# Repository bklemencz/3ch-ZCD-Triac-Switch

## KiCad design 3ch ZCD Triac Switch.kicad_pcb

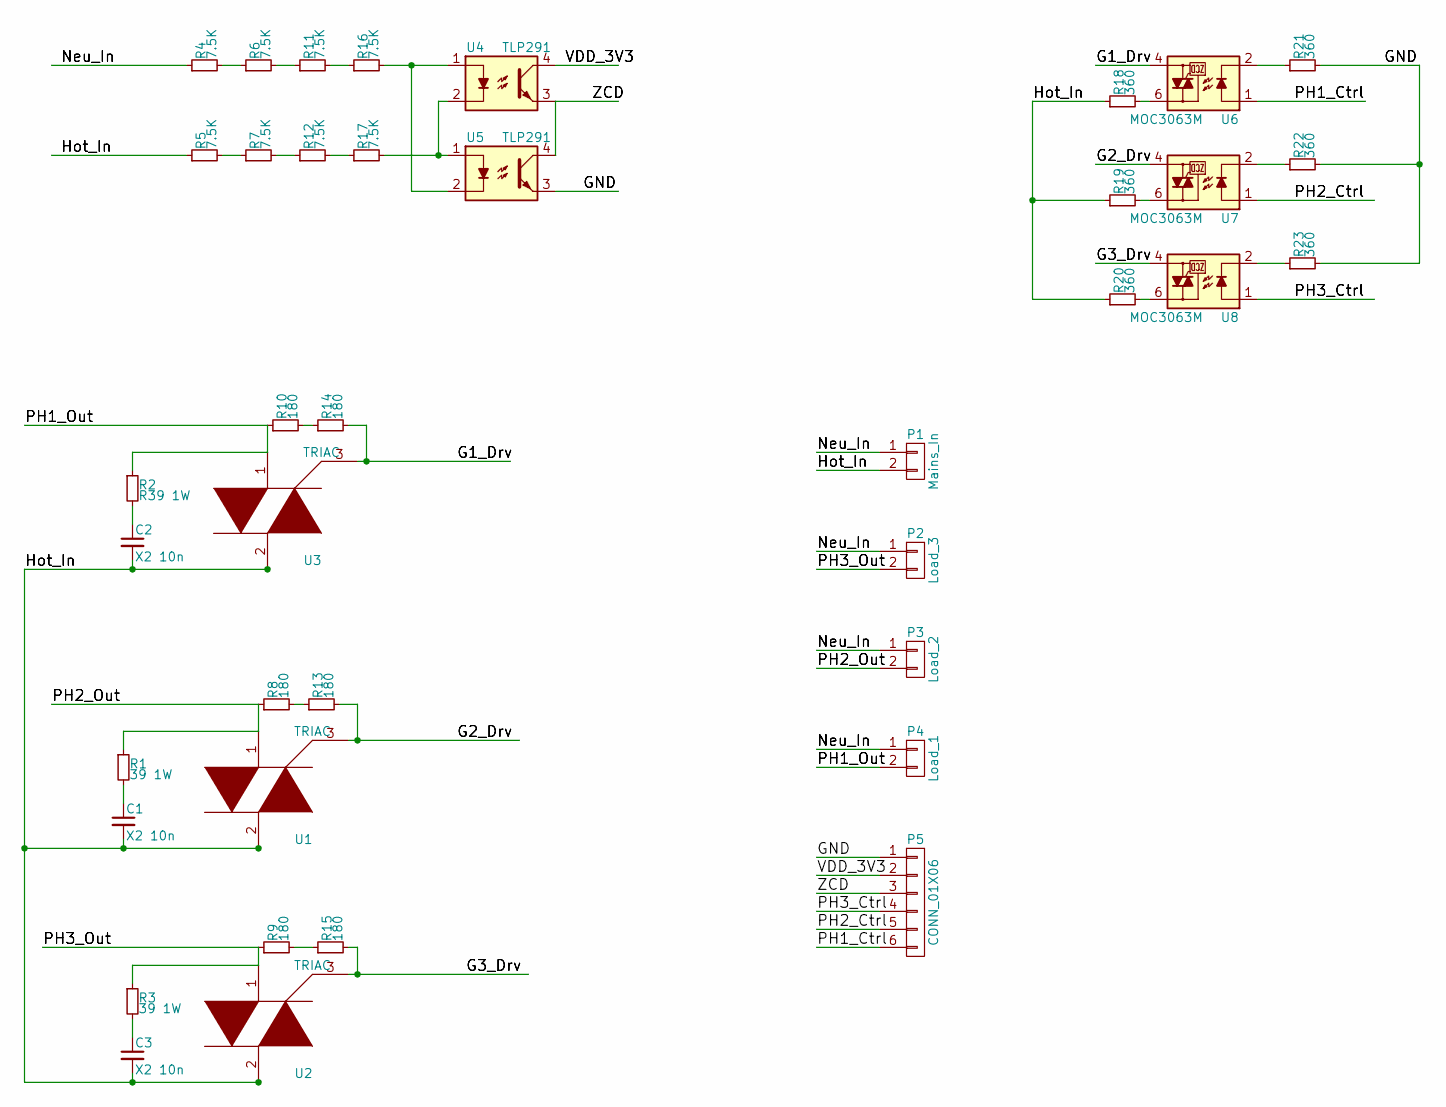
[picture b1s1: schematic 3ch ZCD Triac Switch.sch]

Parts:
C1, C2, C3: X2 10n; C_Rect_L13_W6_H12_P10
P1: Mains_In; TerminalBlock_Pheonix_MKDS1.5-2pol
P2: Load_3; TerminalBlock_Pheonix_MKDS1.5-2pol
P3: Load_2; TerminalBlock_Pheonix_MKDS1.5-2pol
P4: Load_1; TerminalBlock_Pheonix_MKDS1.5-2pol
P5: CONN_01X06; Pin_Header_Straight_1x06
R1, R3: 39 1W; Resistor_Horizontal_RM15mm
R2: R39 1W; Resistor_Horizontal_RM15mm
R4, R5, R6, R7, R11, R12, R16, R17: 7.5K; R_1206
R8, R9, R10, R13, R14, R15: 180; R_1206
R18, R19, R20, R21, R22, R23: 360; R_1206
U1, U2, U3: TRIAC; SOT-428
U4, U5: TLP291; Optocoupler_SMD_ReflowWaveSoldering_KPC357_LTV35x_PC357_Sin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
U6, U7, U8: MOC3063M; DIP-6_W7.62mm_LongPads

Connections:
/G1_Drv: R14.2, U3.3, U6.4
/G2_Drv: R13.2, U1.3, U7.4
/G3_Drv: R15.2, U2.3, U8.4
/GND: P5.1, R21.2, R22.2, R23.2, U5.3
/Hot_In: C1.2, C2.2, C3.2, P1.2, R5.1, R18.1, R19.1, R20.1, U1.2, U2.2, U3.2
/Neu_In: P1.1, P2.1, P3.1, P4.1, R4.1
/PH1_Ctrl: P5.6, U6.1
/PH1_Out: P4.2, R2.1, R10.1, U3.1
/PH2_Ctrl: P5.5, U7.1
/PH2_Out: P3.2, R1.1, R8.1, U1.1
/PH3_Ctrl: P5.4, U8.1
/PH3_Out: P2.2, R3.1, R9.1, U2.1
/VDD_3V3: P5.2, U4.4
/ZCD: P5.3, U4.3, U5.4
unnamed: C1.1, R1.2
unnamed: C2.1, R2.2
unnamed: C3.1, R3.2
unnamed: R4.2, R6.1
unnamed: R5.2, R7.1
unnamed: R10.2, R14.1
unnamed: R6.2, R11.1
unnamed: R11.2, R16.1
unnamed: R7.2, R12.1
unnamed: R12.2, R17.1
unnamed: R8.2, R13.1
unnamed: R9.2, R15.1
unnamed: R16.2, U4.1, U5.2
unnamed: R17.2, U4.2, U5.1
unnamed: R18.2, U6.6
unnamed: R19.2, U7.6
unnamed: R20.2, U8.6
unnamed: R21.1, U6.2
unnamed: R22.1, U7.2
unnamed: R23.1, U8.2

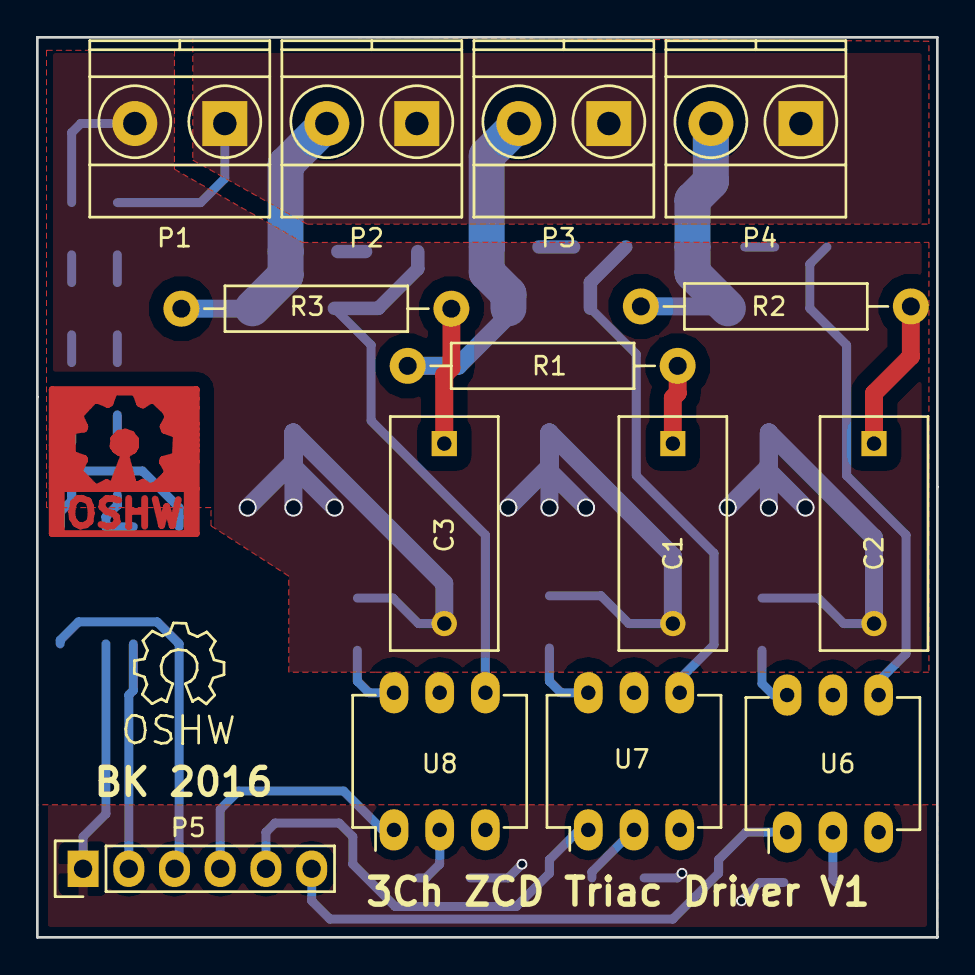
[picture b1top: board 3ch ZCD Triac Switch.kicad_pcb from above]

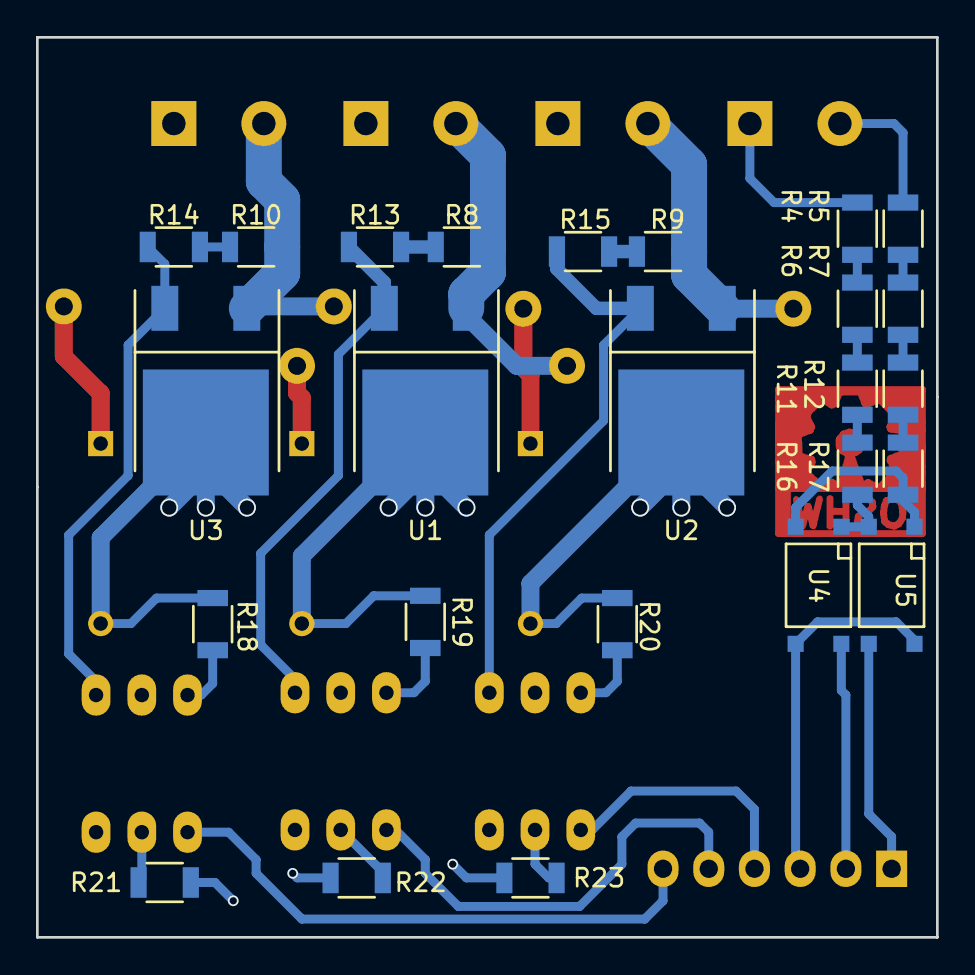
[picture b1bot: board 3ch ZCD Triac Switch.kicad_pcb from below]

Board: 2 copper layers, 50.0 x 50.0 mm, 39 parts (25 on the bottom side), 34 nets.

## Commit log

2016-03-10 :neckbeard: Added .gitattributes & .gitignore files
2016-03-10 First
2016-03-11 Triac Track Change to 2mm
    2.9A with 10CdT
2016-03-17 Sch PDF
2016-03-23 gerber
